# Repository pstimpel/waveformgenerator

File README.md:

# Waveform Generator

Click to play video

First of all, the credit for creating the basic circuit goes to Scullcom Hobby Electronics Youtube channel, who is inactive meanwhile - sadly.

https://www.youtube.com/channel/UCDqryeq1kMDSEQwltWqASrA

Project page at Thingiverse: https://www.thingiverse.com/thing:4243526

Project page at Prusaprinters: https://www.prusaprinters.org/prints/27172-xr2206-waveform-generator

## Why?

Someone said: when starting the hobby electronics, you will need to build 2 things, a power supply and a waveform generator.

## Again, why?

I was keen to dive into electronics again, after 20 years of ignoring this hobby. To get some practice again, I thought building such a generator would be fun. It was fun. 

## What did you change on the original circuit?

Based on Scullcoms circuit I started creating an Arduino controlled waveform gegenerator. My goal was to control as much as possible by the Arduino. So I removed the following parts from the original circuit:

* switch for changing from sine to triangle wave
* switch for changing from sine/triangle to square wave
* switch for enabling pulse width modulation
* switch for changing the frequency range

I replaced them with a relay and some opto isolators.

## Was there any challenge?

Uh, plenty of challenges. 

Figuring out how to replace mechanical switches by opto isolators and relay was kind of a long way for me. First of, I tried to do it by simple transistors, and failed. So opto isolators were the next try, and I was able to replace 3 of 4 switches by these ICs. One left. So I tried a micro relay, and this worked out great.

Another issue I had was to balance out the whole circuit, so I would be able to select halfway decent frequency ranges. Finally, a big enough coarse frequency potentiometer combined with a trim poti did the trick. My goal was to have kind of smooth waveforms, not to hunt Megahertzes for the marketing paper. 

I built the whole circuit at least 4 times on breadboards. And what to tell: those breadboards can be a pain in the ass, at least the cheapos. 

## What can you expect?

You will get a waveform generator able to generate sine, triangle and square waves. The frequency range is from about 1 Hz up to 100 kHz, split into 5 ranges you can switch between (1-10, 10-100, 100 to 1,000, 1,000 to 10,000 and 10,000 to 100,000 Hz, roughly). You can adjust the frequency within these ranges by two potis. The amplitude is about +5 to -5 V (adjustable) at the 50 Ohms output, and from 0 to 5V at the TTL output. There is a basic Pulse width modulation available as well. You can adjust the pulse width. By combining sine or triangle waves and PWM you recieve kind of a ramp modulation. The waveform is quite solid, but with 100kHz you will see some distortion and spikes. It seems this is kind of a typical behavior of the XR2206 chipset. There is a frequency counter used to display the set frequency. However, this is kind of an estimation, especially in very low Hz ranges.

## What you will find in this repository

### Folder enclosure

This folder contains the stl files to 3D print the enclosure. I was using PLA and my Prusa I3 Mk3 printer. On top, there are 2 PDFs containing labels. You could just print them, cut them out of the sheet of paper, use an exacto knife to cut the holes, and mount it to the front of your enclosure

### Folder circuits

There are 2 circuits. One keeps all the control stuff and the Arduino, and the other creates the waveform and gets controlled by the control board. There are gerber files, the KICAD board file, and PDFs with the circuit scheme itself. In each subfolder you wil find a list of parts. 

## What to buy (BOM)

Beside the stuff from the parts lists in the circuit folders, you will need

* potentiometer 10k linear, 6mm axle (gain control)
* potentiometer 1M linear, 6mm axle (frequency control, coarse)
* potentiometer 10k linear, 6mm axle (frequency control, fine)
* potentiometer 1ook linear, 6mm axle (PWM control)
* 3 push buttons, closing type, like in https://www.amazon.de/gp/product/B07MY2WVQ3
* 1 switch, like in https://www.amazon.de/gp/product/B07MY2WVQ3
* 1 smaller heatsink for TO220, LM7812
* 1 midsze heatsink for TO220, LM7805
* 15 V power supply with 5.5x2.1 connector
* matching 5.5x2.1 socket for your power supply
* 25 cylinderhead screws, M3x12
* 16x2 I2C LED for Arduino
* 2 BNC sockets
* wires
* Pinheaders 2.54mm
* matching IC sockets if you dislike soldering the ICs to the PCB directly (2x 8pin, 1x 14pin, 3x 16pin)
* 3 screw terminals, 2 poles, 5mm 
* dupont style wires or similar to connect to pinheaders

## Howto

### Fast lane

Order PCBs and parts, solder all the stuff together, patch the Arduino using the sketch provided, 3d Print the enclosure, put PCBs inside enclosure, mount LCD, potis and switches to the front, solder dupont style wires to them, connect with the PCBs, mount BNC sockets to the front, use some cable to connect them to the PCB, insert 5.5x2.1 soocket in its pocket, lock it using the lock, connect it to the PCB. Lock the PCBs using the pcblock, secure it using one of the screws. Close the enclosure. Connect power, switch the device on, and have fun.

## Remarks, hints

### Arduino

To run the display you will need to add library LiquidCrystal_I2C by Frank de Brabander.

To have frequence counting, you will need to add library FreqCounter by Martin Nawrath.

### Breadboarding

I highly recommend testing the circuit on a breadboard before you go for the soldering stuff. You will learn much more that way than by just following this rough guide. 

### Pricing vs functionality vs fun

If you look for a decent waveform generator delivering Megahertz samples, buy one. 

If you look for the cheapest of all solutions, by such a chinese XR2206 kit for less than 10 USD.

If you want to enjoy DIY, start buying parts and follow the guide I provided. Good luck, wish you well.

### Credits

'rine 77' https://github.com/rine77 contributed updated circuit data, compatible with Kicad6

## CORONA

This project was finished during the spare time provided by Corona. If someone reads this in the future, I really hope Corona is no issue anymore. Until then: stay safe, wash your hands, and take care of your family.

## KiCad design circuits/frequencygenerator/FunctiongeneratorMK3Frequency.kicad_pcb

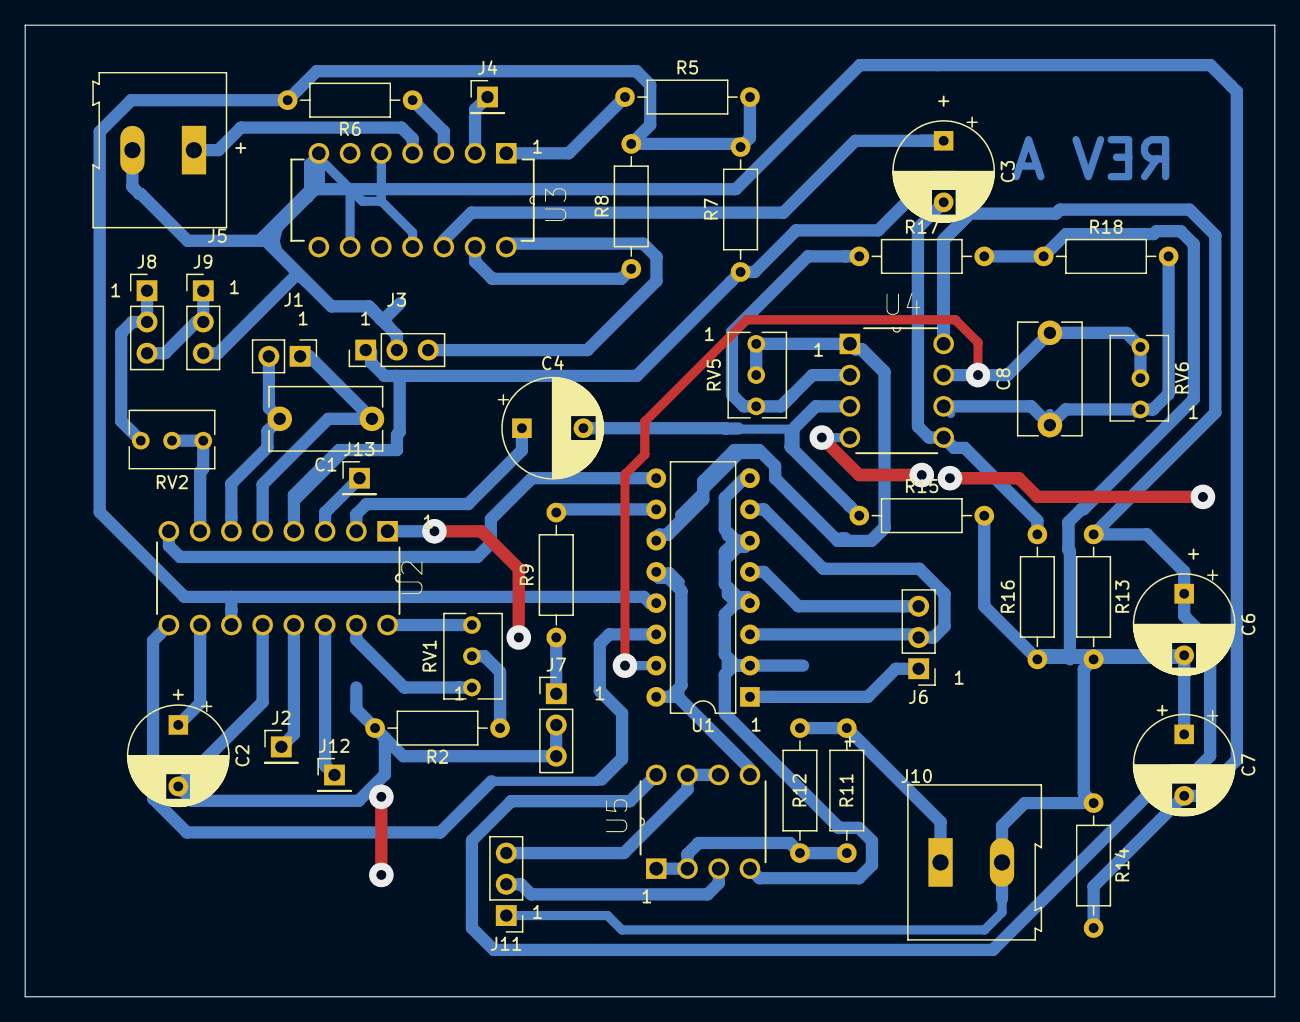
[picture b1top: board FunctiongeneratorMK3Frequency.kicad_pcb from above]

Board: 2 copper layers, 101.6 x 79.0 mm, 43 parts (0 on the bottom side), 42 nets.

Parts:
C1, C8: 100pF; C_Disc_D9.0mm_W5.0mm_P7.50mm
C2: 10uF; CP_Radial_D8.0mm_P5.00mm
C3: 10u; CP_Radial_D8.0mm_P5.00mm
C4: 1u; CP_Radial_D8.0mm_P5.00mm
C6, C7: 220uF; CP_Radial_D8.0mm_P5.00mm
J1: FreqRange; PinHeader_1x02_P2.54mm_Vertical
J2: WaveA1; PinHeader_1x01_P2.54mm_Vertical
J3: 12V-GND-5V; PinHeader_1x03_P2.54mm_Vertical
J4: FreqCounterD5; PinHeader_1x01_P2.54mm_Vertical
J5: TTL OUT; TerminalBlock_Altech_AK300-2_P5.00mm
J6: SIN-TRI-SQU-PWM; PinHeader_1x03_P2.54mm_Vertical
J7: PulseWidth 100k; PinHeader_1x03_P2.54mm_Vertical
J8: FreqCoarse 1M; PinHeader_1x03_P2.54mm_Vertical
J9: FreqFine 10k; PinHeader_1x03_P2.54mm_Vertical
J10: 50 Ohm OUT; TerminalBlock_Altech_AK300-2_P5.00mm
J11: OUT Gain 10k; PinHeader_1x03_P2.54mm_Vertical
J12: WaveA2; PinHeader_1x01_P2.54mm_Vertical
J13: MO; PinHeader_1x01_P2.54mm_Vertical
R2, R5, R6, R8, R13, R14: 1k; R_Axial_DIN0207_L6.3mm_D2.5mm_P10.16mm_Horizontal
R7, R17, R18: 10k; R_Axial_DIN0207_L6.3mm_D2.5mm_P10.16mm_Horizontal
R9: 2k2; R_Axial_DIN0207_L6.3mm_D2.5mm_P10.16mm_Horizontal
R11, R12: 100; R_Axial_DIN0207_L6.3mm_D2.5mm_P10.16mm_Horizontal
R15, R16: 47k; R_Axial_DIN0207_L6.3mm_D2.5mm_P10.16mm_Horizontal
RV1, RV5, RV6: 20k; Potentiometer_Bourns_3266Y_Vertical
RV2: 50k; Potentiometer_Bourns_3266Y_Vertical
U1: LTV-847; DIP-16_W7.62mm
U2: XR2206CP-F; DIP254P762X533-16
U3: 74HC14; DIP254P762X508-14
U4, U5: NE5532; DIP254P762X508-8

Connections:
GND: C2.2, C7.2, J3.2, J5.2, J7.2, J7.3, J9.3, R2.2, R14.2, U1.2, U1.4, U1.6, U1.8, U2.1, U2.12, U3.5, U3.7, U3.9, U3.11, U4.4, U5.4
unnamed: C1.1, J1.1, U2.5
unnamed: C1.2, J1.2, U2.6
unnamed: C2.1, U2.10
unnamed: C3.1, U3.12
unnamed: C3.2, R16.2, U4.5
unnamed: C4.1, U2.2
unnamed: C4.2, R15.1, U4.3
unnamed: C6.1, J3.1, R7.1, R13.1, U2.4, U4.8, U5.8
unnamed: C6.2, C7.1, J10.2, J11.1, R13.2, R14.1, R15.2, R16.1, R17.2, R18.1
unnamed: C8.1, R18.2, RV6.1, U4.6
unnamed: C8.2, RV6.2, RV6.3, U1.15, U4.7
unnamed: J2.1, U2.13
unnamed: J3.3, U3.14
unnamed: J4.1, U3.2
unnamed: J5.1, U3.4
unnamed: J6.1, U1.1
unnamed: J6.2, U1.3, U1.7
unnamed: J6.3, U1.5
unnamed: J7.1, R9.1
unnamed: J8.1, J8.2, RV2.1
unnamed: J8.3, J9.1, J9.2
unnamed: J10.1, R11.2, R12.2
unnamed: J11.2, U5.3
unnamed: J11.3, U5.6, U5.7
unnamed: J12.1, U2.14
unnamed: J13.1, U2.3
unnamed: R2.1, RV1.2
unnamed: R5.1, U3.1
unnamed: R5.2, R6.2, R7.2, R8.2, U1.13, U2.11
unnamed: R6.1, U3.3
unnamed: R8.1, U3.13
unnamed: R9.2, U1.10
unnamed: R11.1, R12.1, U5.1, U5.2
unnamed: R17.1, RV5.3, U4.2
unnamed: RV1.1, U2.16
unnamed: RV1.3, U2.15
unnamed: RV2.2, RV2.3, U2.7
unnamed: RV5.1, RV5.2, U1.11, U4.1
unnamed: U1.9, U2.8
unnamed: U1.12, U1.16, U5.5
unnamed: U1.14, U2.9

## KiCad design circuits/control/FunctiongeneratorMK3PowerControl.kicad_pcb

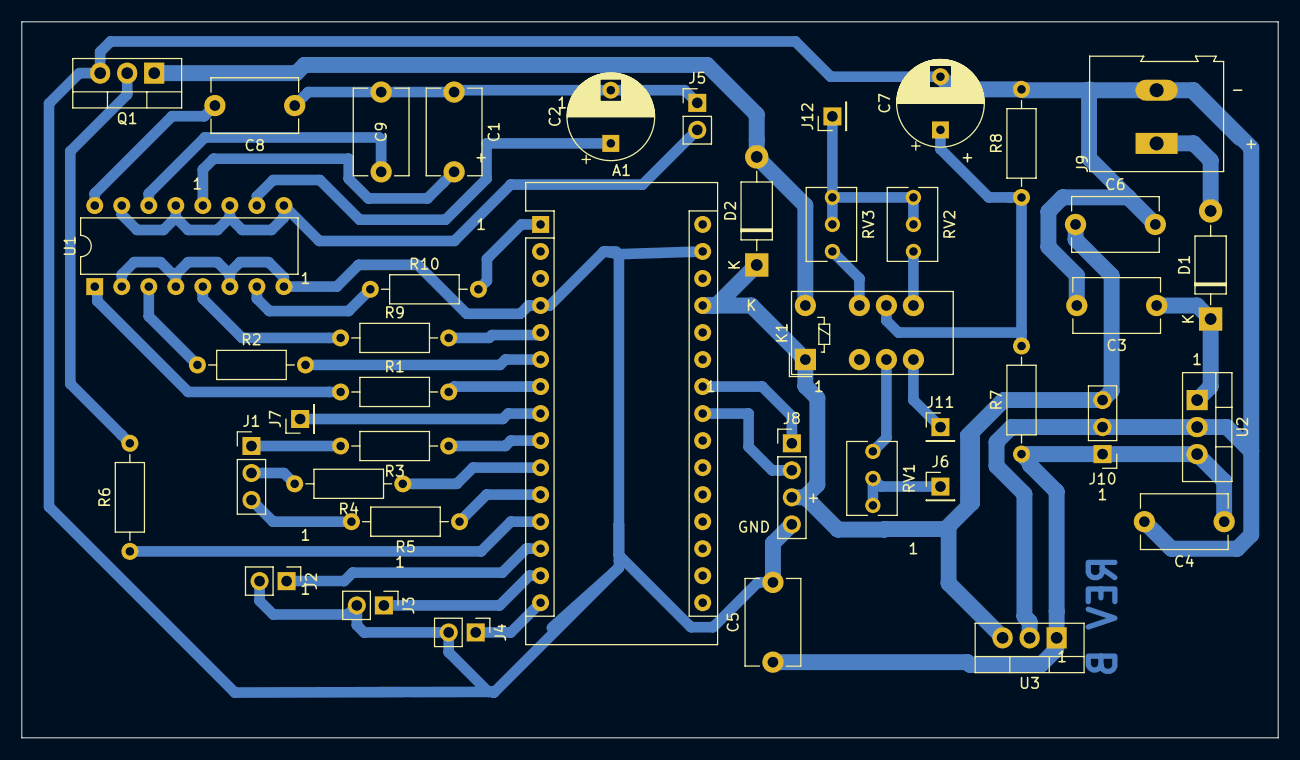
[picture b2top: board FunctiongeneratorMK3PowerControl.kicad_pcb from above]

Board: 2 copper layers, 118.1 x 67.3 mm, 42 parts (0 on the bottom side), 41 nets.

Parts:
A1: Arduino_Nano_v3.x; Arduino_Nano
C1, C5, C6: 100nF; C_Disc_D8.0mm_W5.0mm_P7.50mm
C2: 1uF; CP_Radial_D8.0mm_P5.00mm
C3, C4: 330nF; C_Disc_D8.0mm_W5.0mm_P7.50mm
C7: 10uF; CP_Radial_D8.0mm_P5.00mm
C8: 1nF; C_Disc_D8.0mm_W5.0mm_P7.50mm
C9: 10nF; C_Disc_D8.0mm_W5.0mm_P7.50mm
D1, D2: 1N4007; D_DO-41_SOD81_P10.16mm_Horizontal
J1: SIN-TRI-SQU-PWM; PinHeader_1x03_P2.54mm_Vertical
J2: BTN Range; PinHeader_1x02_P2.54mm_Vertical
J3: BTN Form; PinHeader_1x02_P2.54mm_Vertical
J4: BTN PWM; PinHeader_1x02_P2.54mm_Vertical
J5: FreqRange; PinHeader_1x02_P2.54mm_Vertical
J6: WaveA1; PinHeader_1x01_P2.54mm_Vertical
J7: FreqCount; PinHeader_1x01_P2.54mm_Vertical
J8: Display; PinHeader_1x04_P2.54mm_Vertical
J9: 14V; TerminalBlock_Altech_AK300-2_P5.00mm
J10: 12V GND 5V; PinHeader_1x03_P2.54mm_Vertical
J11: WaveA2; PinHeader_1x01_P2.54mm_Vertical
J12: MO; PinHeader_1x01_P2.54mm_Vertical
K1: G6S-2; Relay_DPDT_Omron_G6S-2
Q1: BC337; TO-220-3_Vertical
R1, R2, R9, R10: 390R; R_Axial_DIN0207_L6.3mm_D2.5mm_P10.16mm_Horizontal
R3, R5: 390; R_Axial_DIN0207_L6.3mm_D2.5mm_P10.16mm_Horizontal
R4: 270; R_Axial_DIN0207_L6.3mm_D2.5mm_P10.16mm_Horizontal
R6, R7, R8: 10k; R_Axial_DIN0207_L6.3mm_D2.5mm_P10.16mm_Horizontal
RV1: 500; Potentiometer_Bourns_3266Y_Vertical
RV2, RV3: 50k; Potentiometer_Bourns_3266Y_Vertical
U1: LTV-847; DIP-16_W7.62mm
U2: LM7812_TO220; TO-220-3_Vertical
U3: LM7805_TO220; TO-220-3_Vertical

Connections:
GND: A1.4, A1.29, C3.2, C4.2, C5.2, C6.2, C7.2, J2.2, J3.2, J4.2, J8.4, J9.2, J10.2, Q1.3, R8.2, U1.2, U1.4, U1.6, U1.8, U2.2, U3.2
unnamed: A1.1, R10.2
unnamed: A1.5, R9.2
unnamed: A1.6, R2.2
unnamed: A1.7, R1.2
unnamed: A1.8, J7.1
unnamed: A1.9, R3.1
unnamed: A1.10, R4.1
unnamed: A1.11, R5.1
unnamed: A1.12, R6.1
unnamed: A1.13, J2.1
unnamed: A1.14, J3.1
unnamed: A1.15, J4.1
unnamed: A1.23, J8.2
unnamed: A1.24, J8.1
unnamed: A1.27, C6.1, D2.1, J8.3, J10.3, K1.1, U3.3
unnamed: C1.1, C2.2, C8.1, C9.1, J5.1
unnamed: C1.2, U1.12
unnamed: C2.1, U1.10
unnamed: C3.1, D1.1, U2.1
unnamed: C4.1, C5.1, J10.1, R7.1, U2.3, U3.1
unnamed: C7.1, K1.9, R7.2, R8.1
unnamed: C8.2, U1.16
unnamed: C9.2, U1.14
unnamed: D1.2, J9.1
unnamed: D2.2, K1.12, Q1.1
unnamed: J1.1, R3.2
unnamed: J1.2, R4.2
unnamed: J1.3, R5.2
unnamed: J5.2, U1.9, U1.11, U1.13, U1.15
unnamed: J6.1, RV1.1, RV1.2
unnamed: J11.1, K1.5
unnamed: J12.1, RV2.2, RV2.3, RV3.2, RV3.3
unnamed: K1.4, RV1.3
unnamed: K1.8, RV2.1
unnamed: K1.10, RV3.1
unnamed: Q1.2, R6.2
unnamed: R1.1, U1.1
unnamed: R2.1, U1.3
unnamed: R9.1, U1.5
unnamed: R10.1, U1.7

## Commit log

2020-03-25 Initial
2020-03-25 finalize draft
2020-03-25 Added specs
2020-03-26 more media and a changed part of the enclosure
2020-03-26 Add more media to finish the readme file
2020-03-26 Finalize V1 of the readme
2020-03-26 Publish V1
2023-01-09 circuit kicad updates
    updated circuits to last kicad version
2023-01-10 Update README.md
    added Credits, fixed speller
